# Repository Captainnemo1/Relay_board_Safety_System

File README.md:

# Relay_board_Safety_System
This is repo containing the design details for constructing a relay board with CAN integration

I created a relay system that is driven by an Atmega32u4 and has CANBUS compatibility.
An Atmega32u4 is used to power the relay box and track the status of the shutdown systems. The relay box is also connected to the CAN bus using the MCU. This allows us to communicate the fault to the driver via the driver interface and allows the vehicle's control systems to be aware of the shutdown state as well.

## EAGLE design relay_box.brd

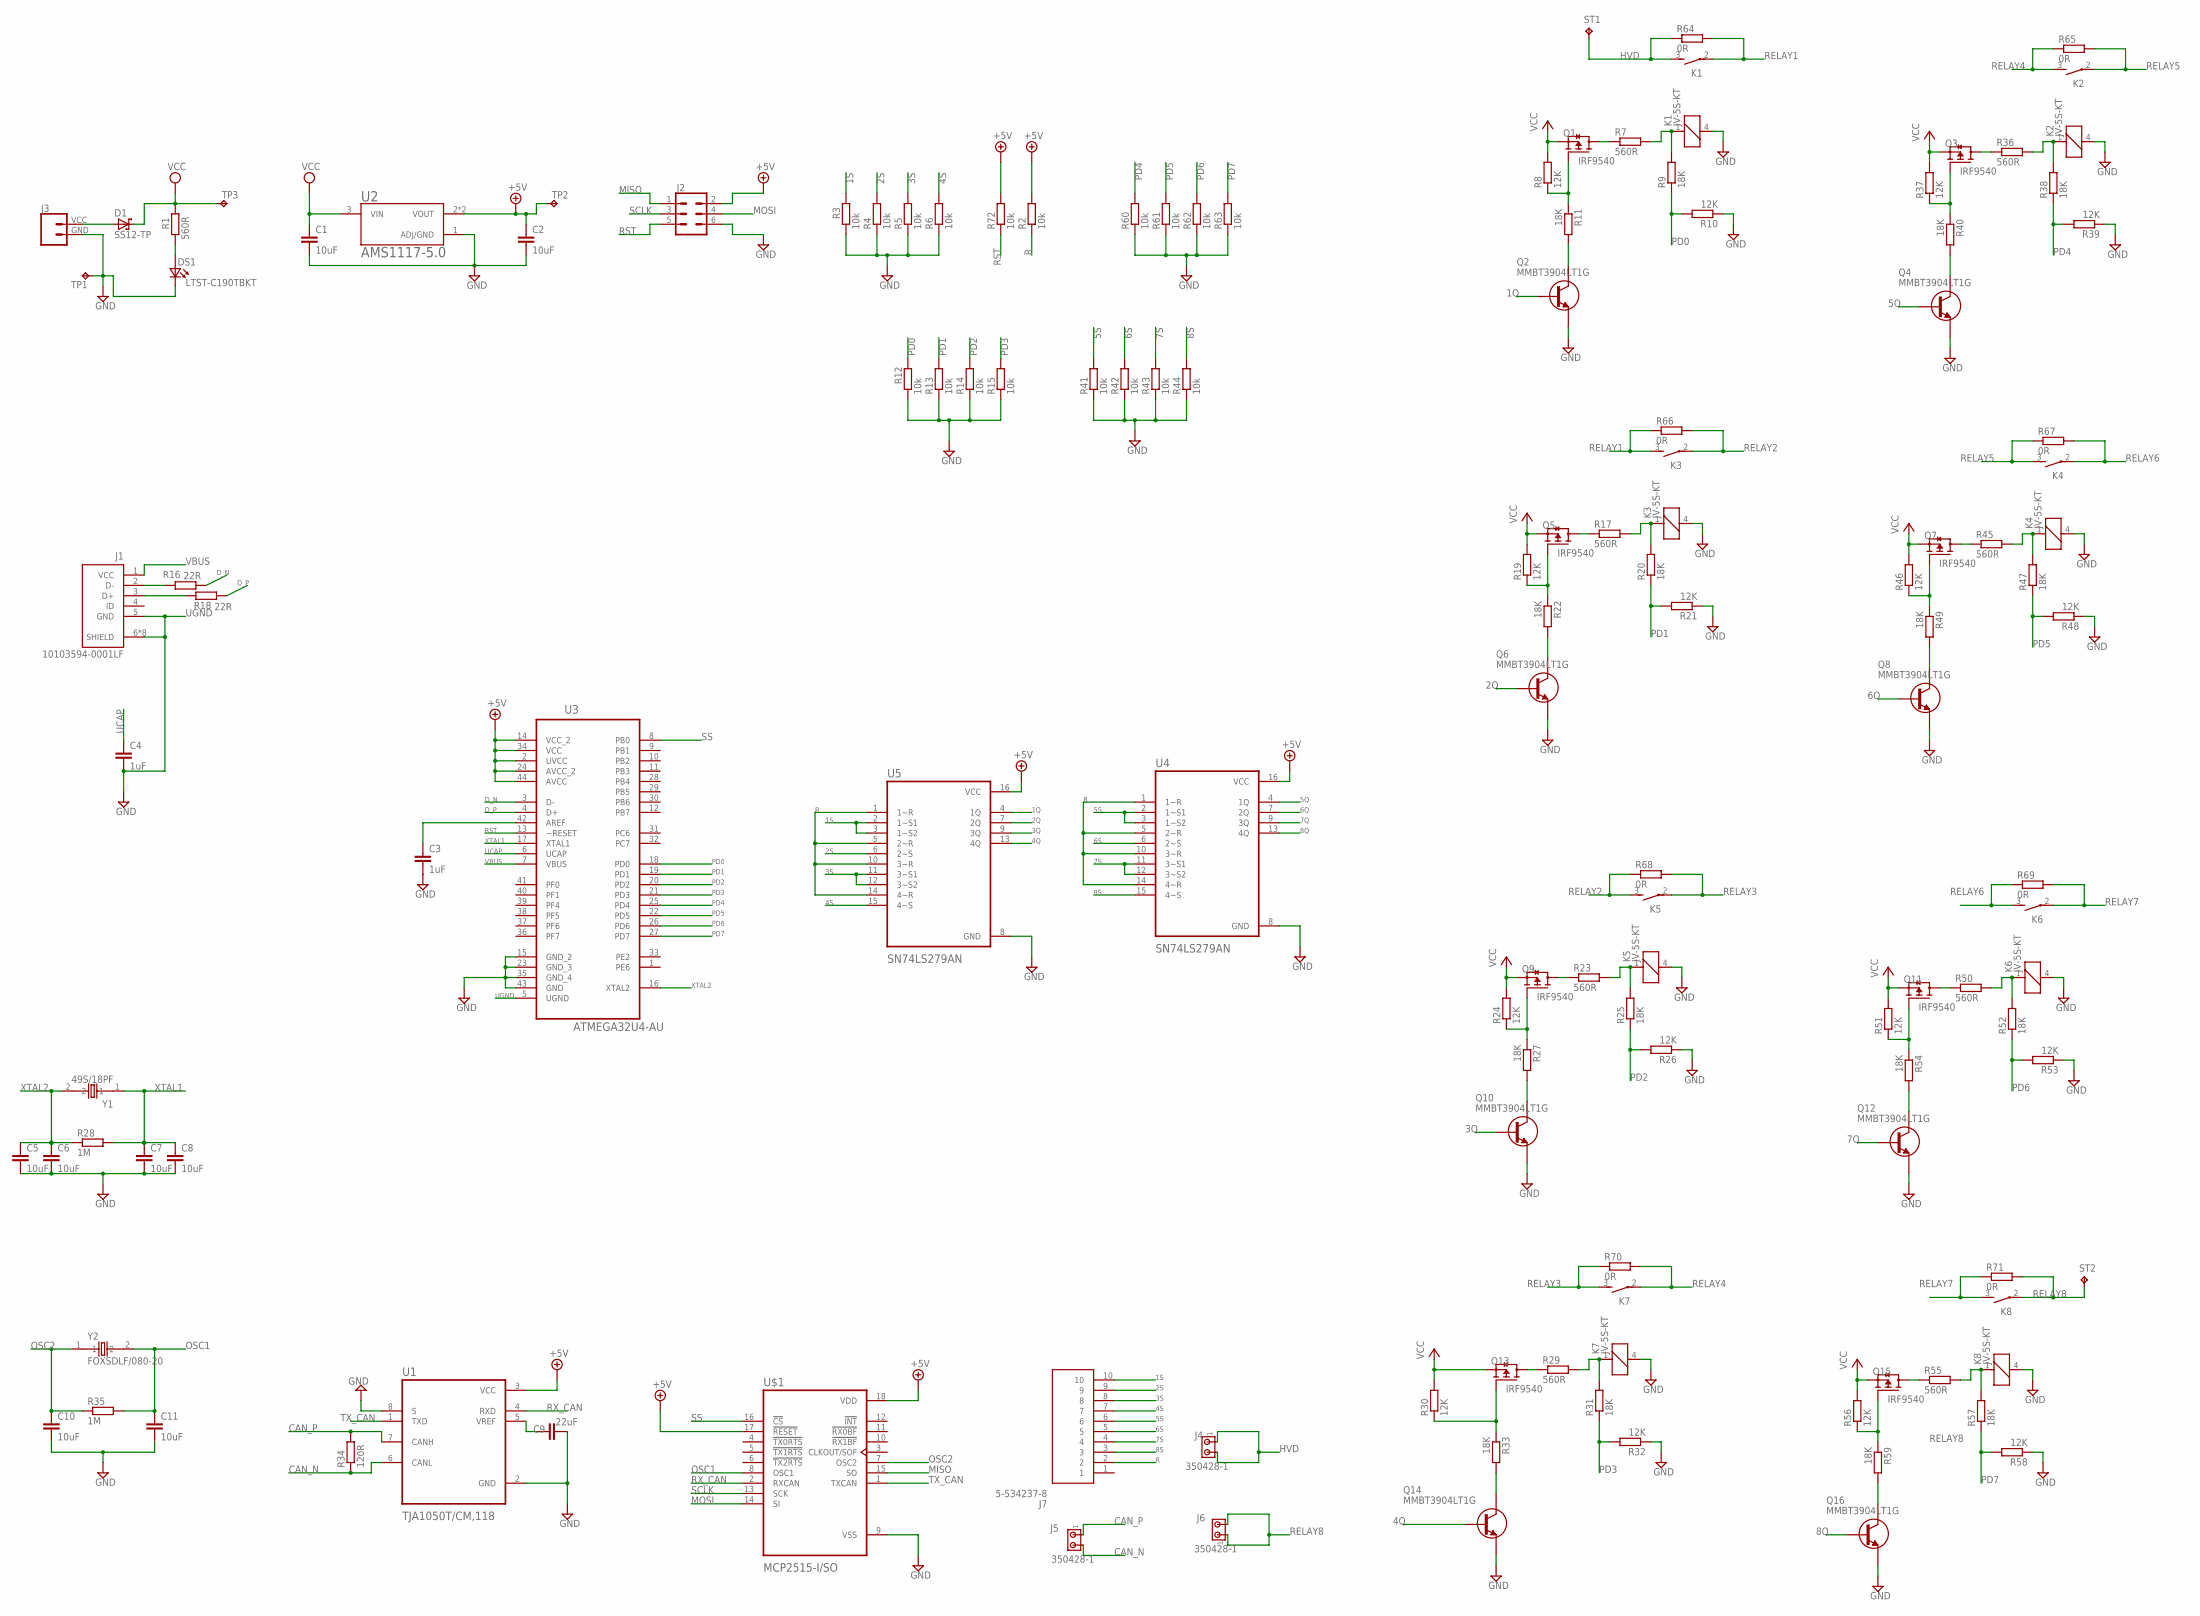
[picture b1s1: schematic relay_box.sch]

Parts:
C1, C2, C5, C6, C7, C8, C10, C11: 10uF; C0805
C3, C4: 1uF; C0603
C9: 22uF; C0603
D1: SS12-TP; DO214AC
DS1: LTST-C190TBKT; 0603
J1: 10103594-0001LF; AMPHENOL_10103594-0001LF
J2: CONN_03X2FEMALE_SMD; 2X3_SMD
J3: CONN_024UCON-15767; JST-2-SMD-VERT
J4, J5, J6: 350428-1
J7: 5-534237-8; RHDR10W76P0X254_1X10_2540X356X
K1, K2, K3, K4, K5, K6, K7, K8: JV-5S-KT; JV-KT
Q1, Q3, Q5, Q7, Q9, Q11, Q13, Q15: IRF9540; TO254P1052X465X1989-3
Q2, Q4, Q6, Q8, Q10, Q12, Q14, Q16: MMBT3904LT1G; SOT23
R1: 560R; R0805
R2, R3, R4, R5, R6, R12, R13, R14, R15, R41, R42, R43, R44, R60, R61, R62, R63, R72: 10k; R0805
R7, R17, R23, R29, R36, R45, R50, R55: 560R; 0207/10
R8, R10, R19, R21, R24, R26, R30, R32, R37, R39, R46, R48, R51, R53, R56, R58: 12K; R0805
R9, R11, R20, R22, R25, R27, R31, R33, R38, R40, R47, R49, R52, R54, R57, R59: 18K; R0805
R16, R18: 22R; R0805
R28, R35: 1M; R0805
R34: 120R; R0805
R64, R65, R66, R67, R68, R69, R70, R71: 0R; 0207/10
ST1, ST2: TPB1,27; B1,27
TP1, TP2, TP3: TPB1,27; B1,27
U1: TJA1050T/CM,118; SOIC127P600X175-8N
U2: AMS1117-5.0; SOT229P700X180-4N
U3: ATMEGA32U4-AU; QFP80P1200X1200X120-44N
U4, U5: SN74LS279AN; DIP794W45P254L1969H508Q16
U$1: MCP2515-I/SO; SOIC127P1030X265-18N
Y1: 49S/18PF; XTAL_49S/18PF
Y2: FOXSDLF/080-20; XTAL1170X500X450

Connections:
1Q: Q2.1 (B), U5.4 (1Q)
1S: J7.10, R3.2, U5.2 (1~S1), U5.3 (1~S2)
2Q: Q6.1 (B), U5.7 (2Q)
2S: J7.9, R4.2, U5.6 (2~S)
3Q: Q10.1 (B), U5.9 (3Q)
3S: J7.8, R5.2, U5.11 (3~S1), U5.12 (3~S2)
4Q: Q14.1 (B), U5.13 (4Q)
4S: J7.7, R6.2, U5.15 (4~S)
5Q: Q4.1 (B), U4.4 (1Q)
5S: J7.6, R41.2, U4.2 (1~S1), U4.3 (1~S2)
6Q: Q8.1 (B), U4.7 (2Q)
6S: J7.5, R42.2, U4.6 (2~S)
7Q: Q12.1 (B), U4.9 (3Q)
7S: J7.4, R43.2, U4.11 (3~S1), U4.12 (3~S2)
8Q: Q16.1 (B), U4.13 (4Q)
8S: J7.3, R44.2, U4.15 (4~S)
+5V: C2.1, J2.2, R2.2, R72.2, TP2.TP, U1.3 (VCC), U2.2 (VOUT), U2.4 (VOUT), U3.2 (UVCC), U3.14 (VCC_2), U3.24 (AVCC_2), U3.34 (VCC), U3.44 (AVCC), U4.16 (VCC), U5.16 (VCC), U$1.17 (!RESET)
CAN_N: J5.2, R34.1, U1.6 (CANL)
CAN_P: J5.1, R34.2, U1.7 (CANH)
D_N: R16.1, U3.3 (D-)
D_P: R18.1, U3.4 (D+)
GND: C1.2, C2.2, C3.2, C5.2, C6.2, C7.2, C8.2, C9.2, C10.2, C11.2, DS1.1 (K2), J2.6, J3.GND (1), K1.4 (2), K2.4 (2), K3.4 (2), K4.4 (2), K5.4 (2), K6.4 (2), K7.4 (2), K8.4 (2), Q2.2 (E), Q4.2 (E), Q6.2 (E), Q8.2 (E), Q10.2 (E), Q12.2 (E), Q14.2 (E), Q16.2 (E), R3.1, R4.1, R5.1, R6.1, R10.1, R12.1, R13.1, R14.1, R15.1, R21.1, R26.1, R32.1, R39.1, R41.1, R42.1, R43.1, R44.1, R48.1, R53.1, R58.1, R60.1, R61.1, R62.1, R63.1, TP1.TP, U1.2 (GND), U1.8 (S), U2.1 (ADJ/GND), U3.15 (GND_2), U3.23 (GND_3), U3.35 (GND_4), U3.43 (GND), U4.8 (GND), U5.8 (GND), U$1.9 (VSS)
HVD: J4.1, J4.2, K1.3 (S), R64.1, ST1.TP
MISO: J2.1, U$1.15 (SO)
MOSI: J2.4, U$1.14 (SI)
unnamed: Q1.1 (G), R8.1, R11.1
unnamed: Q1.2 (D), R7.1
unnamed: Q2.3 (C), R11.2
unnamed: K1.1, R7.2, R9.2
unnamed: Q3.1 (G), R37.1, R40.1
unnamed: Q4.3 (C), R40.2
unnamed: K2.1, R36.2, R38.2
unnamed: Q3.2 (D), R36.1
unnamed: Q5.1 (G), R19.1, R22.1
unnamed: Q6.3 (C), R22.2
unnamed: K3.1, R17.2, R20.2
unnamed: Q5.2 (D), R17.1
unnamed: Q7.1 (G), R46.1, R49.1
unnamed: Q8.3 (C), R49.2
unnamed: K4.1, R45.2, R47.2
unnamed: Q7.2 (D), R45.1
unnamed: Q9.1 (G), R24.1, R27.1
unnamed: Q10.3 (C), R27.2
unnamed: K5.1, R23.2, R25.2
unnamed: Q9.2 (D), R23.1
unnamed: Q11.1 (G), R51.1, R54.1
unnamed: Q12.3 (C), R54.2
unnamed: K6.1, R50.2, R52.2
unnamed: Q11.2 (D), R50.1
unnamed: Q13.1 (G), R30.1, R33.1
unnamed: Q14.3 (C), R33.2
unnamed: K7.1, R29.2, R31.2
unnamed: Q13.2 (D), R29.1
unnamed: Q15.1 (G), R56.1, R59.1
unnamed: Q16.3 (C), R59.2
unnamed: K8.1, R55.2, R57.2
unnamed: Q15.2 (D), R55.1
unnamed: DS1.2 (A2), R1.1
unnamed: D1.A, J3.VCC (2)
unnamed: J1.2 (D-), R16.2
unnamed: J1.3 (D+), R18.2
unnamed: C9.1, U1.5 (VREF)
unnamed: C3.1, U3.42 (AREF)
OSC1: C11.1, R35.2, U$1.8 (OSC1), Y2.2
OSC2: C10.1, R35.1, U$1.7 (OSC2), Y2.1
PD0: R9.1, R10.2, R12.2, U3.18 (PD0)
PD1: R13.2, R20.1, R21.2, U3.19 (PD1)
PD2: R14.2, R25.1, R26.2, U3.20 (PD2)
PD3: R15.2, R31.1, R32.2, U3.21 (PD3)
PD4: R38.1, R39.2, R60.2, U3.25 (PD4)
PD5: R47.1, R48.2, R61.2, U3.22 (PD5)
PD6: R52.1, R53.2, R62.2, U3.26 (PD6)
PD7: R57.1, R58.2, R63.2, U3.27 (PD7)
R: J7.2, R2.1, U4.1 (1~R), U4.5 (2~R), U4.10 (3~R), U4.14 (4~R), U5.1 (1~R), U5.5 (2~R), U5.10 (3~R), U5.14 (4~R)
RELAY1: K1.2, K3.3 (S), R64.2, R66.1
RELAY2: K3.2, K5.3 (S), R66.2, R68.1
RELAY3: K5.2, K7.3 (S), R68.2, R70.1
RELAY4: K2.3 (S), K7.2, R65.1, R70.2
RELAY5: K2.2, K4.3 (S), R65.2, R67.1
RELAY6: K4.2, K6.3 (S), R67.2, R69.1
RELAY7: K6.2, K8.3 (S), R69.2, R71.1
RELAY8: J6.1, J6.2, K8.2, R71.2, ST2.TP
RST: J2.5, R72.1, U3.13 (~RESET)
RX_CAN: U1.4 (RXD), U$1.2 (RXCAN)
SCLK: J2.3, U$1.13 (SCK)
SS: U3.8 (PB0), U$1.16 (!CS)
TX_CAN: U1.1 (TXD), U$1.1 (TXCAN)
UCAP: C4.1, U3.6 (UCAP)
UGND: C4.2, J1.5 (GND), J1.6 (SHIELD), J1.7 (SHIELD), J1.8 (SHIELD), J1.9 (SHIELD), J1.10 (SHIELD), J1.11 (SHIELD), J1.S1 (SHIELD), J1.S2 (SHIELD), U3.5 (UGND)
VBUS: J1.1 (VCC), U3.7 (VBUS)
VCC: C1.1, D1.C, Q1.3 (S), Q3.3 (S), Q5.3 (S), Q7.3 (S), Q9.3 (S), Q11.3 (S), Q13.3 (S), Q15.3 (S), R1.2, R8.2, R19.2, R24.2, R30.2, R37.2, R46.2, R51.2, R56.2, TP3.TP, U2.3 (VIN)
XTAL1: C7.1, C8.1, R28.2, U3.17 (XTAL1), Y1.1
XTAL2: C5.1, C6.1, R28.1, U3.16 (XTAL2), Y1.2

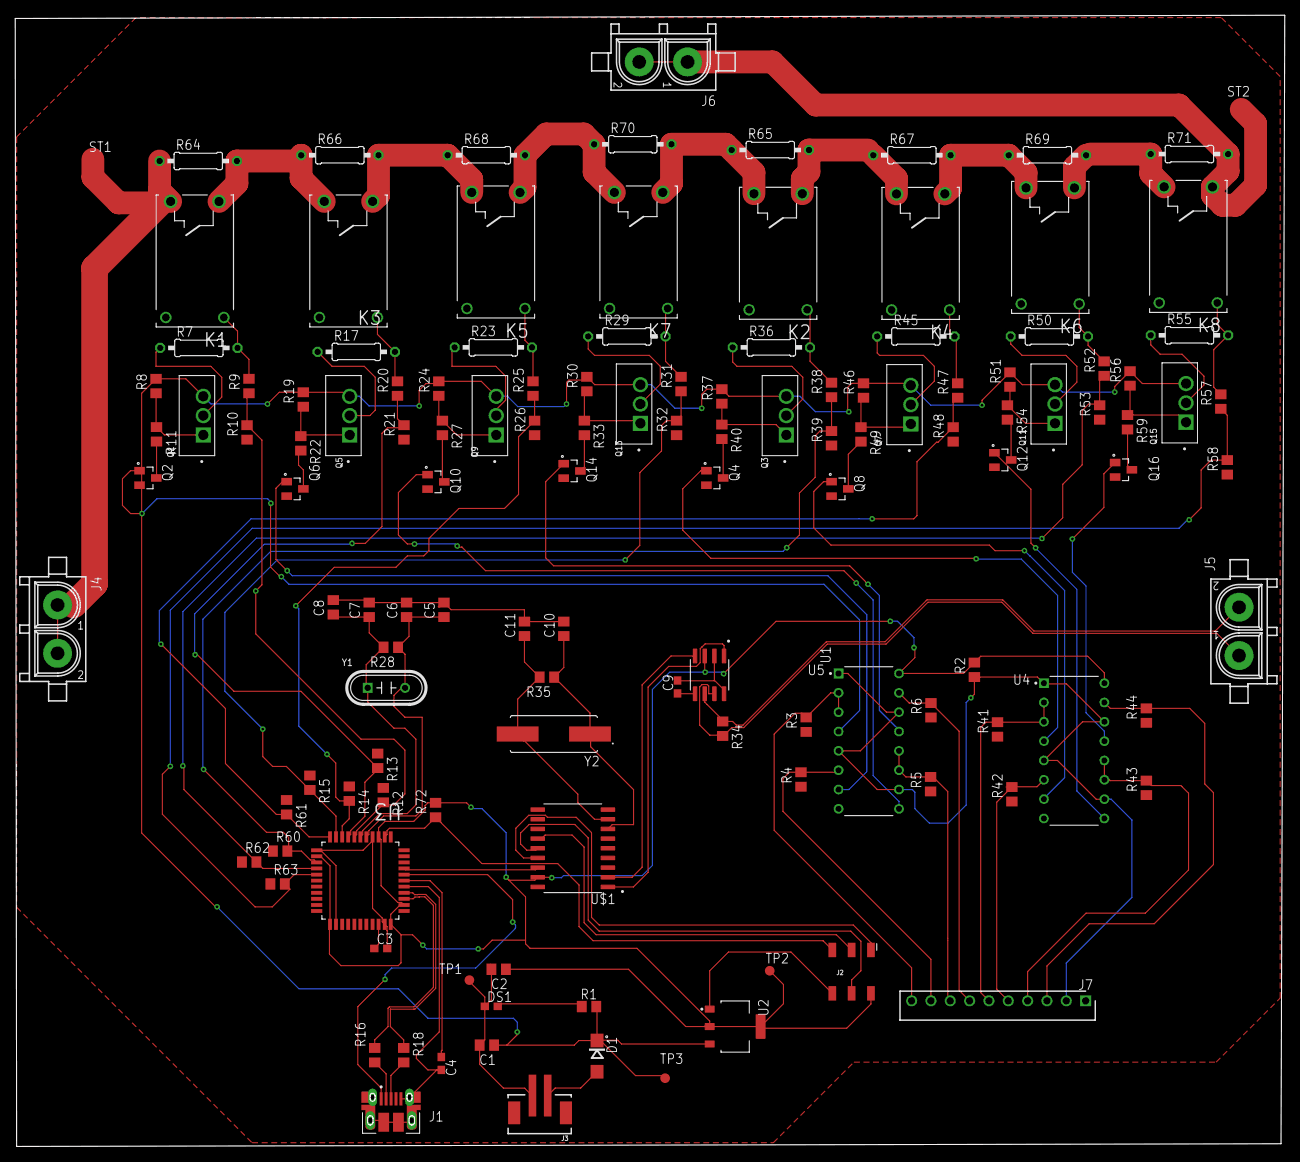
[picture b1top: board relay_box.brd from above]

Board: 2 copper layers, 166.8 x 148.6 mm, 129 parts (0 on the bottom side), 93 nets.

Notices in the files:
parts and their libraries:
SparkFun-Connectors: Licensing: Creative Commons ShareAlike 4.0 International - https://creativecommons.org/licenses/by-sa/4.0
